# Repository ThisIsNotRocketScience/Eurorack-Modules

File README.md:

View this project on [CADLAB.io](https://cadlab.io/node/837). 

# Eurorack-Modules

This is the central repo for all the "This is not Rocket Science" eurorack modular synth modules.

Please refer to the "Production" folder if you are looking for boards to build. You will find all the design & firmware files for our latest production versions. Artwork is NOT included. Be creative. 

All our current development & experiments can be found in the "Development" folder

Sourcecode to the firmware can be found in the Eurorack-KDS repository

Tools needed:

- Eagle 7+
- Kinetis Development Studio (or whatever the latest NXP/freescale IDE is)
- A JTAG probe to flash the initial firmware

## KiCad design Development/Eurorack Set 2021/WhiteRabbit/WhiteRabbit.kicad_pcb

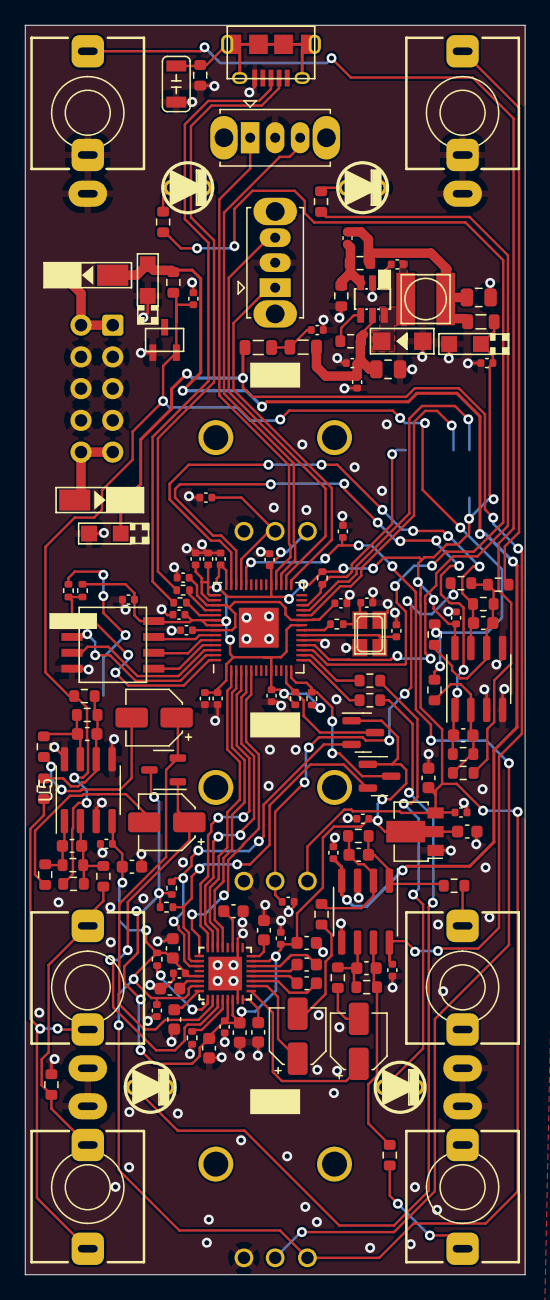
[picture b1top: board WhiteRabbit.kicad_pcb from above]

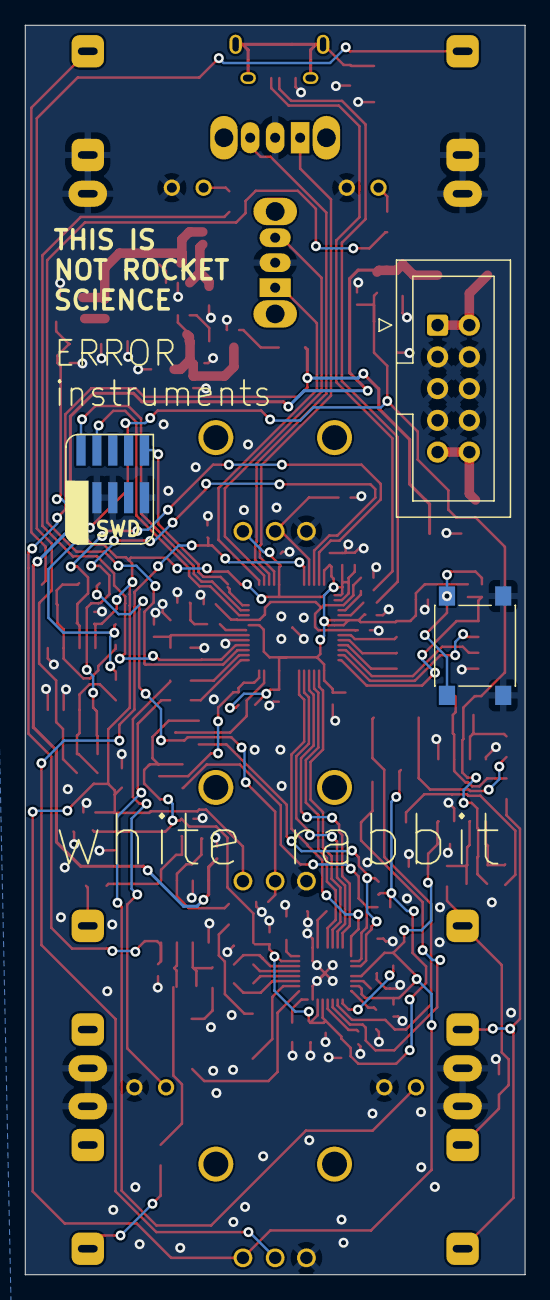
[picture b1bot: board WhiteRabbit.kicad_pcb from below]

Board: 2 copper layers, 40.0 x 100.0 mm, 146 parts (3 on the bottom side), 95 nets.

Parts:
C2, C3, C4, C7: 1u C72491; CP_Elec_4x3.9
C5, C23, C48: 197427; CASE-A_3216
C6: 1301804; C_0402_1005Metric
C8: 10u; C_0805_2012Metric
C9, C18, C19, C20, C21, C54: 4.7u; C_0603_1608Metric
C10, C12, C13, C14, C22, C52: 2.2u; C_0603_1608Metric
C11: 22u; C_0805_2012Metric
C15, C16, C56, C57, C58, C59: unknown; C_0603_1608Metric
C17, C40, C41, C42, C43, C44, C45, C46, C62, C63: 1759017; C_0402_1005Metric
C24, C50: 10u; C_0603_1608Metric
C25, C26, C27, C28, C29, C30, C31, C35, C36, C37, C38, C47, C49, C51, C53, C55, C60, C61, C99: 100n; C_0402_1005Metric
C32, C33: 27p; C_0402_1005Metric
C34, C100: 1u; C_0402_1005Metric
C39: 4.7n 100v; C3216
D1, D2: 9551824; DO-214AC
D3, D4, D5, D6: LED3MM; 3MMLED
D7: BAT54C C49991; SOT-23-3
D18: schottky; SOD123
J1: MICRO-USB-5P; C132563
J8: Conn_02x05_Odd_Even; IDC-Header_2x05_P2.54mm_Vertical
J9, J10, J11, J12, J13, J14: AudioJack2_SwitchT; Jack_3.5mm_QingPu_WQP-PJ301M-12_Vertical
L1, L2, L4: 0.1uH C76737; L_0805_2012Metric
L3: 4.7uH; L0420
Q1, Q2: TSM2302CX; SOT-23
Q4: 12mhz; NX3225
R1, R44, R45: unknown; ALPS_POT_SQUAREHOLES
R4, R6: 27; R_0402_1005Metric
R12, R13, R14, R15, R16, R17, R18, R19, R20, R21, R22, R23, R24, R25, R26, R27, R28, R29, R30, R31, R32, R35, R36, R37, R38, R39, R40, R41, R42, R43: unknown; R_0603_1608Metric
R33, R103, R105, R106: 1k; R_0402_1005Metric
R34: 10k DNP; R_0402_1005Metric
R52: 10k; R_0402_1005Metric
R74: 1M; R_0603_1608Metric
R104, R107: DNP; R_0402_1005Metric
R108, R109: 2k; R_0402_1005Metric
REF1: ALC5616-CGT; QFN-32_L4.0-W4.0-P0.40-TL-EP2.7
SW1: SW_Push; SW_Push_1P1T_NO_6x6mm_H9.5mm
SW2, SW3: SW_SPDT_MSM; SW_Slide_1P2T_CK_OS102011MS2Q
SWD2: unknown; M50-3600542
U1: 9778330; SOT95P237X112-3N
U2: AZ1117-1.8; SOT-89-3
U3: RP2040; QFN-56-1EP_7x7mm_P0.4mm_EP3.2x3.2mm
U4: TL072; SOIC-8_3.9x4.9mm_P1.27mm
U5, U6: C2937047; SOIC-8_3.9x4.9mm_P1.27mm
U$5: BL9342; SOT23-6
U$25: W25Q256JVEIQTR; SOIC-8

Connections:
+1V8: C18.1, C19.1, C20.1, C38.1, C47.1, C50.1, C51.1, D7.3, Q1.1 (G), Q2.1 (G), R105.2, R106.2, REF1.5 (DACREF), REF1.6 (AVDD), REF1.15 (CPVDD), U2.2 (VO)
+3V3: C17.1, C23.+ (1), C24.1, C25.2, C26.2, C27.2, C28.2, C30.2, C31.2, C35.2, C36.2, C37.2, C49.1, C52.2, C53.1, C54.1, C55.1, C63.1, C100.1, L4.2, R1.P$3 (A), R34.2, R44.P$3 (A), R45.P$3 (A), R52.1, R104.1, R108.2, R109.2, REF1.29 (DBVDD), REF1.31 (MICVDD), SWD2.1 (VCC), U2.3 (VI), U3.1 (IOVDD), U3.10 (IOVDD), U3.22 (IOVDD), U3.33 (IOVDD), U3.42 (IOVDD), U3.43 (ADC_AVDD), U3.44 (VREG_IN), U3.48 (USB_VDD), U3.49 (IOVDD), U5.4 (V-), U6.8 (V+), U$25.8 (VCC)
+12V: C48.+ (1), C60.1, D1.2 (-), L1.1, U4.8 (V+)
-5V: C6.2, R15.2, R19.2, R25.2, R26.2, R28.2, U1.2 (ANODE)
-12V: C5.- (2), C61.2, D2.1 (+), R26.1, U4.4 (V-)
/MCU & Eeprom/ADC_JACK_X: C16.2, R22.1, U3.40 (GPIO28_ADC2), U6.1
/MCU & Eeprom/ADC_JACK_Y: C15.2, R12.1, U3.41 (GPIO29_ADC3), U6.7
/MCU & Eeprom/ADC_KNOB_MIX: C62.1, R1.P$2 (S), U3.38 (GPIO26_ADC0)
/MCU & Eeprom/ADC_KNOB_X: C41.1, R44.P$2 (S), U3.39 (GPIO27_ADC1)
/MCU & Eeprom/BOOTSEL_BUT: R33.2, SW1.2
/MCU & Eeprom/CODEC_IN_LEFT: C4.2, R18.1
/MCU & Eeprom/CODEC_IN_LEFT_CLAMPED: C4.1, D7.1, REF1.3 (IN2P)
/MCU & Eeprom/CODEC_IN_RIGHT: C7.2, R24.1
/MCU & Eeprom/CODEC_IN_RIGHT_CLAMPED: C7.1, D7.2, REF1.2 (IN1P)
/MCU & Eeprom/CODEC_OUT_LEFT: C3.2, R35.2
/MCU & Eeprom/CODEC_OUT_RIGHT: C2.2, R27.2
/MCU & Eeprom/CODEC_SCL: Q2.2 (S), R106.1, REF1.26 (SCL)
/MCU & Eeprom/CODEC_SCL_HIGH: Q2.3 (D), R109.1, U3.14 (GPIO11)
/MCU & Eeprom/CODEC_SDA: Q1.2 (S), R105.1, REF1.27 (SDA)
/MCU & Eeprom/CODEC_SDA_HIGH: Q1.3 (D), R108.1, U3.13 (GPIO10)
/MCU & Eeprom/COREVDD: C29.1, C34.1, C99.1, U3.23 (DVDD), U3.45 (VREG_VOUT), U3.50 (DVDD)
/MCU & Eeprom/I2S_ADCDAT: REF1.21 (ADCDAT1), U3.3 (GPIO1)
/MCU & Eeprom/I2S_BCLK: REF1.24 (BCLK1), U3.4 (GPIO2)
/MCU & Eeprom/I2S_DACDAT: REF1.22 (DACDAT1), U3.2 (GPIO0)
/MCU & Eeprom/I2S_LRCK: REF1.23 (LRCK1), U3.5 (GPIO3)
/MCU & Eeprom/I2S_MCLK: REF1.25 (MCLK), U3.6 (GPIO4)
/MCU & Eeprom/JACK_DELAY: J13.T, R14.2
/MCU & Eeprom/KNOB_Y: C40.1, R38.2, R45.P$2 (S)
/MCU & Eeprom/LED_DELAYS: R41.2, U3.17 (GPIO14)
/MCU & Eeprom/LED_INPUTS: R39.2, U3.15 (GPIO12)
/MCU & Eeprom/LED_OUTPUTS: R40.2, U3.16 (GPIO13)
/MCU & Eeprom/LED_VERBS: R42.2, U3.18 (GPIO15)
/MCU & Eeprom/MEM_CLK: U3.52 (QSPI_SCLK), U$25.6 (CLK)
/MCU & Eeprom/MEM_CS: R33.1, R34.1, U3.56 (QSPI_SS), U$25.1 (/CS)
/MCU & Eeprom/MEM_IO0: U3.53 (QSPI_SD0), U$25.5 (DI)
/MCU & Eeprom/MEM_IO1: U3.55 (QSPI_SD1), U$25.2 (DO)
/MCU & Eeprom/MEM_IO2: U3.54 (QSPI_SD2), U$25.3 (IO2)
/MCU & Eeprom/MEM_IO3: U3.51 (QSPI_SD3), U$25.7 (IO3)
/MCU & Eeprom/RUN: R52.2, SWD2.10 (RESET), U3.26 (RUN)
/MCU & Eeprom/SWCLK: SWD2.4 (SWCLK), U3.24 (SWCLK)
/MCU & Eeprom/SWDIO: SWD2.2 (SWDIO), U3.25 (SWD)
/MCU & Eeprom/SWITCH_DELAY_OR_VERB_1: SW2.3, U3.31 (GPIO20)
/MCU & Eeprom/SWITCH_DELAY_OR_VERB_2: SW2.1, U3.32 (GPIO21)
/MCU & Eeprom/SWITCH_TYPE_1: SW3.1, U3.29 (GPIO18)
/MCU & Eeprom/SWITCH_TYPE_2: SW3.3, U3.30 (GPIO19)
/MCU & Eeprom/USB_N: J1.2 (DM), R6.1
/MCU & Eeprom/USB_P: J1.3 (DP), R4.1
/Power/min12in: D2.2 (-), J8.1, J8.2
/Power/plus12in: D1.1 (+), J8.9, J8.10
/Power/regulator_feedback_1: C11.2, C46.1, L3.2, L4.1, R31.1
/Power/regulator_feedback_2: C46.2, R31.2, R32.1, U$5.3 (FB)
/Power/regulator_filter: C42.2, L1.2, L2.1
/Power/regulator_inputside: C8.2, C43.2, C44.2, L2.2, R23.2, U$5.5 (VIN)
/Power/regulator_switchoutput: C45.1, D18.-, L3.1, U$5.6 (SW)
GND: C5.+ (1), C6.1, C8.1, C9.1, C11.1, C13.1, C14.1, C17.2, C18.2, C19.2, C20.2, C21.2, C22.2, C23.- (2), C24.2, C25.1, C26.1, C27.1, C28.1, C29.2, C30.1, C31.1, C32.2, C33.2, C34.2, C35.1, C36.1, C37.1, C38.2, C39.1, C40.2, C41.2, C42.1, C43.1, C44.1, C47.2, C48.- (2), C49.2, C50.2, C51.2, C52.1, C53.2, C54.2, C55.2, C60.2, C61.1, C62.2, C63.2, C99.2, C100.2, D3.1 (K), D4.1 (K), D5.1 (K), D6.1 (K), D18.+, J1.5 (GND@1), J8.3, J8.4, J8.5, J8.6, J8.7, J8.8, J9.S, J10.S, J11.S, J12.S, J13.S, J13.TN, J14.S, J14.TN, Q4.2 (G2), Q4.4 (G1), R1.P$1 (E), R32.2, R43.2, R44.P$1 (E), R45.P$1 (E), R74.1, R107.1, REF1.7 (AGND), REF1.18 (CPVREF), REF1.33 (EP), SW1.1, SW2.2, SW3.2, SWD2.3 (GND1), SWD2.5 (GND2), SWD2.9 (GND3), U1.1 (CATHODE), U2.1 (GND), U3.19 (TESTEN), U3.57 (GND), U4.3 (+), U4.5 (+), U5.3 (+), U5.5 (+), U5.8 (V+), U6.3 (+), U6.4 (V-), U6.5 (+), U$5.2 (GND), U$25.4 (GND)
unnamed: C56.2, R17.1, R18.2, U5.1
unnamed: C57.2, R20.1, R24.2, U5.7
unnamed: C58.2, R29.1, R30.2, U4.7
unnamed: C59.2, R36.1, R37.2, U4.1
unnamed: D3.2 (A), R39.1
unnamed: D4.2 (A), R40.1
unnamed: D5.2 (A), R41.1
unnamed: D6.2 (A), R42.1
unnamed: C39.2, J1.B@2 (GND@2), J1.B@4 (GND@2), J1.B@5 (GND@2), J1.B@6 (GND@3), J1.B@7 (GND@2), J1.B@8 (GND@2), J1.B@9 (GND@2), J1.B@12 (GND@2), R74.2
unnamed: J9.TN, J10.T, R21.2
unnamed: J9.T, J10.TN, R13.2, R43.1
unnamed: J11.T, R37.1
unnamed: J12.T, R30.1
unnamed: J14.T, R16.2
unnamed: C32.1, Q4.1 (X1), R103.1
unnamed: C33.1, Q4.3 (X2), U3.20 (XIN)
unnamed: C12.2, REF1.13 (CPN1)
unnamed: C10.2, REF1.11 (CPN2)
unnamed: C12.1, REF1.14 (CPP1)
unnamed: C10.1, REF1.12 (CPP2)
unnamed: C13.2, REF1.19 (CPVEE)
unnamed: C14.2, REF1.16 (CPVPP)
unnamed: C22.1, REF1.30 (DCVDD)
unnamed: R107.2, REF1.4 (IN2N/JD2)
unnamed: R104.2, REF1.1 (JD1)
unnamed: C2.1, REF1.9 (LOUTL/P)
unnamed: C3.1, REF1.10 (LOUTR/N)
unnamed: C21.1, REF1.32 (MICBIAS1)
unnamed: C9.2, REF1.8 (VREF)
unnamed: R6.2, U3.46 (USB_DM)
unnamed: R4.2, U3.47 (USB_DP)
unnamed: R103.2, U3.21 (XOUT)
unnamed: C59.1, R35.1, R36.2, U4.2 (-)
unnamed: C58.1, R27.1, R29.2, U4.6 (-)
unnamed: C56.1, R13.1, R17.2, R19.1, U5.2 (-)
unnamed: C57.1, R20.2, R21.1, R25.1, U5.6 (-)
unnamed: C16.1, R14.1, R22.2, R28.1, U6.2 (-)
unnamed: C15.1, R12.2, R15.1, R16.1, R38.1, U6.6 (-)
unnamed: C45.2, U$5.1 (BST)
unnamed: R23.1, U$5.4 (EN)

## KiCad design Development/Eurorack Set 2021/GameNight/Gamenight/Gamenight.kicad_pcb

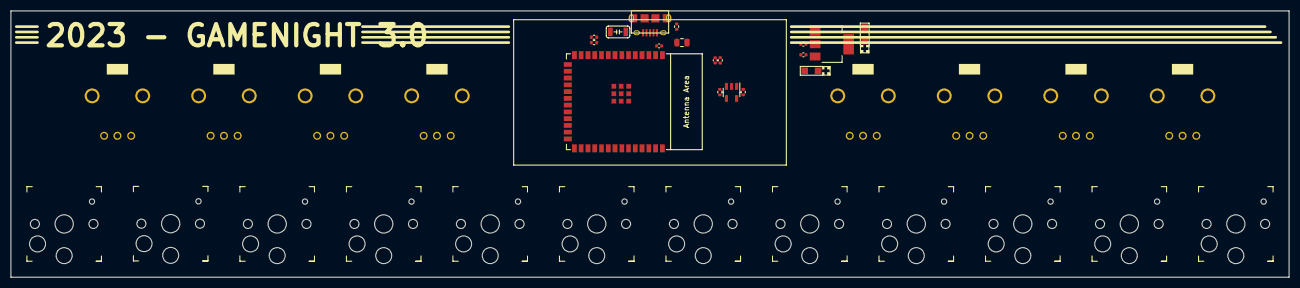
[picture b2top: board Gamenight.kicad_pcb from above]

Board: 2 copper layers, 240.0 x 50.0 mm, 39 parts (1 on the bottom side), 12 nets, no tracks yet.

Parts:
C48, C52: 1759017; C_0402_1005Metric
C50, C55: 197427; CASE-A_3216
C59: 4.7n 100v; C3216
C60: 1u; C_0402_1005Metric
C61: 22u; C_0805_2012Metric
C62: 100n; C_0402_1005Metric
J14: MICRO-USB-5P; C132563
P1, P2, P3, P4, P5, P6, P7, P8: POTSQUAREHOLE_SMALLKNOB; ALPS_POT_SQUAREHOLES
R73, R74: 0; R_0402_1005Metric
R75: 1M; R_0402_1005Metric
R76, R77: 2k; R_0402_1005Metric
R78: 10k; R_0402_1005Metric
SW1, SW3, SW4, SW5, SW6, SW7, SW8, SW9, SW10, SW11, SW12, SW13: SW_Push; Kailh_socket_PG1350
SW2: SW_Push; SW_Push_1P1T_NO_6x6mm_H9.5mm
U1: AMS1117-3.3; SOT-223-3_TabPin2
U2: AT24CS01-STUM; SOT-23-5
U12: ESP32-S3-WROOM-1

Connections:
+3V3: C48.1, C55.+ (1), C61.1, C62.1, R76.2, R77.1, R78.1, U1.2 (VO), U2.4 (VCC), U12.2 (3V3)
+5V: C50.+ (1), C52.2, J14.1 (VCC), U1.3 (VI)
/BOOTSEL_BUT: SW2.2, U12.27 (GPIO0/BOOT)
/EEPROM_SCL: R77.2, U2.1 (SCL), U12.33 (MTDO/GPIO40/CLK_OUT2)
/EEPROM_SDA: R76.1, U2.3 (SDA), U12.32 (MTCK/GPIO39/CLK_OUT3/SUBSPICS1)
/EN: C60.1, R78.2, U12.3 (EN)
/USB_N: J14.2 (DM), R74.1
/USB_P: J14.3 (DP), R73.1
GND: C48.2, C50.- (2), C52.1, C55.- (2), C59.1, C60.2, C61.2, C62.2, J14.5 (GND@1), R75.1, SW2.1, U1.1 (GND), U2.2 (GND), U2.5 (WP), U12.1 (GND), U12.40 (GND), U12.41 (GND)
unnamed: C59.2, J14.B@2 (GND@2), J14.B@4 (GND@2), J14.B@5 (GND@2), J14.B@6 (GND@3), J14.B@7 (GND@2), J14.B@8 (GND@2), J14.B@9 (GND@2), J14.B@12 (GND@2), R75.2
unnamed: R74.2, U12.13 (GPIO19/U1RTS/ADC2_CH8/CLK_OUT2/USB_D-)
unnamed: R73.2, U12.14 (GPIO20/U1CTS/ADC2_CH9/CLK_OUT1/USB_D+)

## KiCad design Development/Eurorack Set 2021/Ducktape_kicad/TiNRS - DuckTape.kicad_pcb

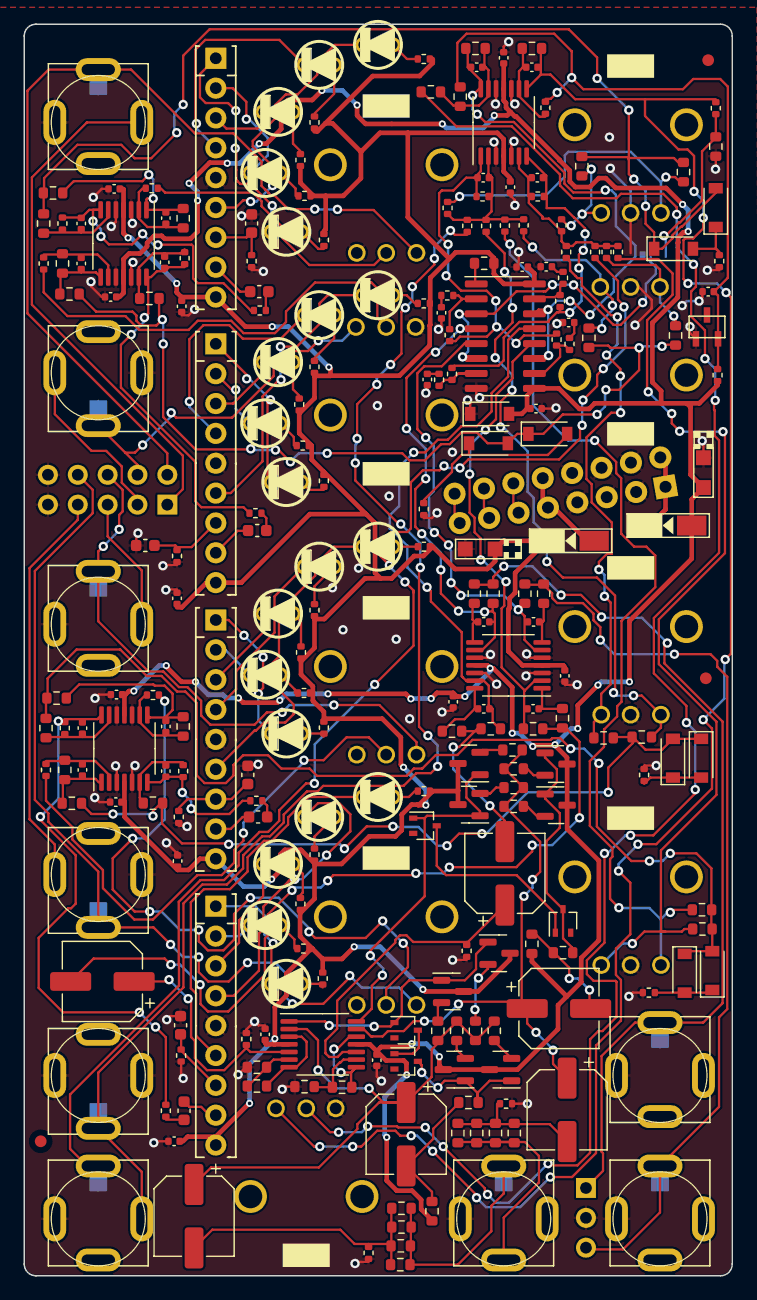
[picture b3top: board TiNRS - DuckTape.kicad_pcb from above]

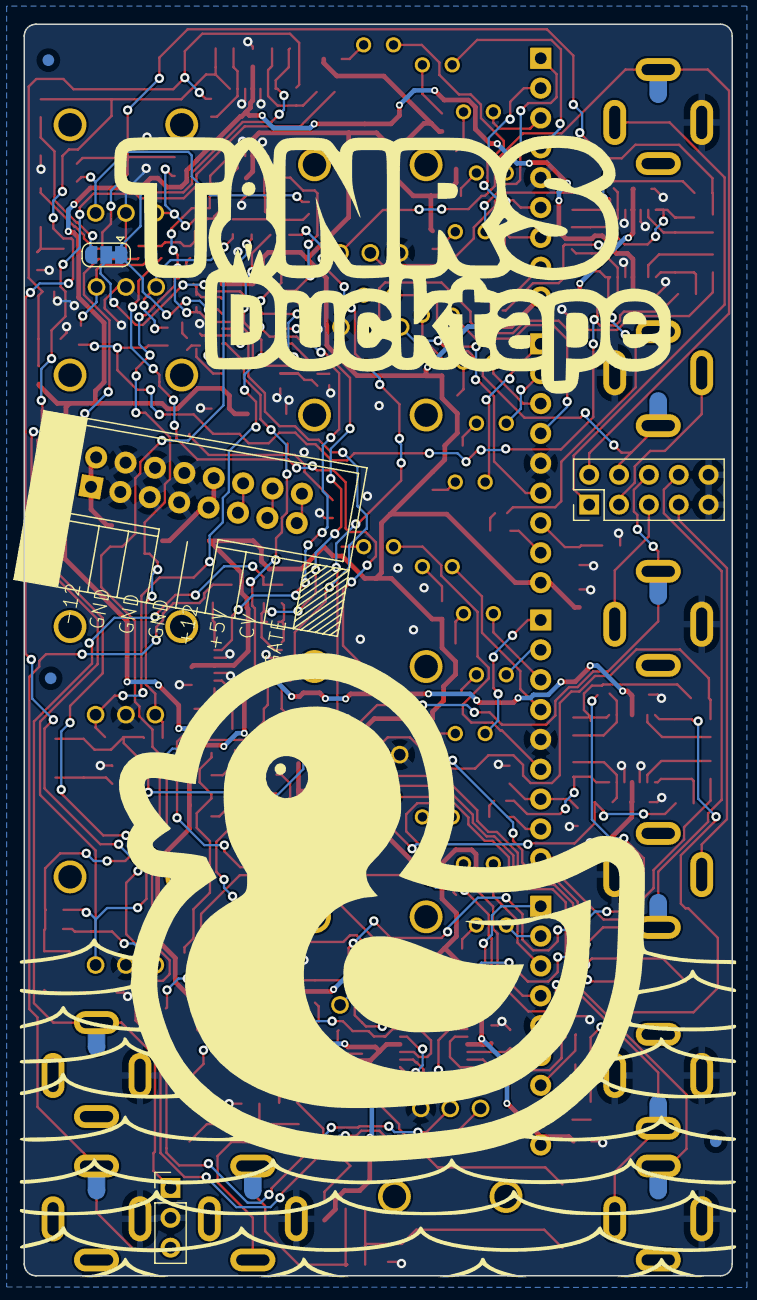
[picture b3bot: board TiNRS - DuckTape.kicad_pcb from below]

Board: 2 copper layers, 60.2 x 106.5 mm, 261 parts (7 on the bottom side), 164 nets.

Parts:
C1, C2, C3, C4, C7, C8, C9, C10, C11, C12, C13, C14, C15, C16, C17, C18, C19, C20, C21, C22, C25, C28, C31, C34, C35, C36, C37, C38, C39, C40, C41, C42, C50, C51, C52, C53: unknown; C_0402_1005Metric
C5, C48: 197427; CASE-A_3216
C6: 1301804; C_0402_1005Metric
C23, C24, C26, C27, C29, C30, C32, C33: unknown; C_0603_1608Metric
C43, C44, C45, C46, C47, C49: 100u; CP_Elec_6.3x3
D1, D2: D-SMA; DO-214AC
D3, D4, D5, D6, D7, D8, D9, D10, D11: 1N4148W; D_SOD-123
D12, D13, D14, D15, D16, D17, D18, D19, D20, D21, D22, D23, D24, D25, D26, D27, D28, D29, D30, D31: LED3MM; 3MMLED
D32, D33, D34, D35: BAS16W; SOT-323_SC-70
FID1, FID2, FID3, FID4, FID5, FID6: Fiducial; Fiducial_1mm_Mask2mm
J1: Conn_01x03; PinHeader_1x03_P2.54mm_Vertical
J2: Conn_02x05_Odd_Even; PinHeader_2x05_P2.54mm_Vertical
J14: unknown; POWER_16_SHROUDED
JACK1, JACK2, JACK3, JACK4, JACK5, JACK6, JACK7, JACK8, JACK9: AUDIO-JACK_SMALLSYMBOL; 3.5MM-JACK-SWITCH-13MM-NOHOLES-TESTPAD
JP1: SolderJumper_3_Bridged12; SolderJumper-3_P1.3mm_Bridged12_RoundedPad1.0x1.5mm
OUTLINE1: unknown; EURORACK12HPPCB
Q1, Q2, Q5, Q6: MMBT3904; SOT-23
Q3, Q4, Q7, Q8: MMBT3906; SOT-23
R1, R3, R5, R10, R11, R16, R17, R22, R23, R34, R36, R38, R40, R42, R44, R46, R48, R51, R52, R55, R56, R82, R84, R87, R90, R93, R96, R97, R98, R99, R100, R102, R103, R104, R105, R106, R107, R108, R110, R111, R112, R113, R114, R116, R117, R118, R119, R120, R121, R122, R123, R124, R125, R126, R127, R128, R129, R130: unknown; R_0603_1608Metric
R2, R7, R9, R13, R15, R19, R21, R25, R26, R27, R28, R30, R31, R32, R33, R35, R37, R39, R41, R43, R45, R47, R49, R50, R53, R54, R57, R58, R59, R60, R61, R62, R63, R64, R65, R66, R67, R68, R69, R70, R71, R72, R73, R74, R75, R76, R77, R78, R79, R80, R81, R83, R85, R86, R88, R89, R91, R92, R94, R95, R101, R109, R115, R131, R132, R133, R134: unknown; R_0402_1005Metric
R4, R6, R8, R12, R14, R18, R20, R24, R29: unknown; ALPS_POT_SQUAREHOLES
U1: 9778330; SOT95P237X112-3N
U2: SSI2164; SOIC-16_3.9x9.9mm_P1.27mm
U3, U4, U5, U10, U11: TL074; TSSOP-14_4.4x5mm_P0.65mm
U6, U7, U8, U9: KA2284; SIP9_Housing

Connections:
+10V: C22.2, R29.P$3 (A), R55.1, R81.2, U5.8
+12V: C7.2, C9.2, C15.2, C19.2, C25.1, C28.1, C31.1, C34.1, C35.2, C37.2, C48.+ (1), D1.2 (-), Q1.3 (C), Q2.3 (C), Q5.3 (C), Q6.3 (C), R1.2, R58.1, R59.1, R60.1, R61.1, R62.1, R64.1, R65.1, R66.1, R67.1, R68.1, R70.1, R71.1, R72.1, R73.1, R74.1, R76.1, R77.1, R78.1, R79.1, R80.1, U2.16 (V+), U3.4 (V+), U4.4 (V+), U5.4 (V+), U6.9 (VCC), U7.9 (VCC), U8.9 (VCC), U9.9 (VCC), U10.4 (V+), U11.4 (V+)
-5V: C6.2, R26.2, R52.2, R53.2, U1.2 (ANODE)
-12V: C5.- (2), C8.2, C10.2, C16.2, C21.2, C36.2, C38.2, D2.1 (+), D3.2 (A), Q3.3 (C), Q4.3 (C), Q7.3 (C), Q8.3 (C), R26.1, R108.2, R122.2, U2.9 (V-), U3.11 (V-), U4.11 (V-), U5.11 (V-), U10.11 (V-), U11.11 (V-)
/CHAN_1: D4.2 (A), D5.1 (K), R5.1, R84.2, R123.2, R124.2
/CHAN_2: D6.2 (A), D7.1 (K), R11.1, R87.2, R125.2, R126.2
/CHAN_3: D8.2 (A), D9.1 (K), R17.1, R90.2, R127.2, R128.2
/CHAN_4: D10.2 (A), D11.1 (K), R23.1, R93.2, R129.2, R130.2
/DEF1: J2.1, JACK2.SWITCH
/DEF2: J2.3, JACK3.SWITCH
/DEF3: J2.5, JACK4.SWITCH
/DEF4: J2.7, JACK5.SWITCH
/HEADPHONE_LEFT: C43.2, R42.1, R44.1
/HEADPHONE_RIGHT: C46.2, R46.1, R48.1
/HeadphoneAmp/LEFT_TIP: JACK1.TIP, R98.2, R99.2, R104.2, R106.2
/HeadphoneAmp/RIGHT_RING: JACK1.SECOND, R112.2, R113.2, R118.2, R120.2
/IN1: J2.2, JACK2.TIP, R4.P$3 (A)
/IN2: J2.4, JACK3.TIP, R8.P$3 (A)
/IN3: J2.6, JACK4.TIP, R14.P$3 (A)
/IN4: J2.8, JACK5.TIP, R20.P$3 (A)
/IN_LEFT: JACK7.TIP, JACK9.SWITCH, R47.1
/IN_RIGHT: JACK9.TIP, R49.2
/LEFT_BUF: C17.2, R27.2, R30.2, R50.1, U5.1
/MASTER_LEVEL: C18.2, JP1.1 (A), R51.1, U2.11 (VC3), U2.14 (VC4), U5.14
/OUT_LEFT: J1.1, JACK6.TIP, R34.1, R36.1
/OUT_RIGHT: J1.3, JACK8.TIP, R38.1, R40.1
/Power/min12in: D2.2 (-), J14.1 (-12V), J14.2 (-12V)
/Power/plus12in: D1.1 (+), J14.9 (+12V), J14.10 (+12V)
/RIGHT_BUF: C20.2, R28.2, R31.2, R54.1, U5.7
/SUM_LEFT: C17.1, R33.1, R37.1, R41.1, R45.1, R47.2, R50.2, U5.2 (-)
/SUM_RIGHT: C20.1, R32.1, R35.1, R39.1, R43.1, R49.1, R54.2, U5.6 (-)
/VCA1_OUT: C11.1, R36.2, U2.4 (I_OUT1), U4.9 (-)
/VCA2_OUT: C12.1, R40.2, U2.5 (I_OUT2), U4.6 (-)
/VCA3_OUT: C13.1, R44.2, U2.12 (I_OUT3), U4.2 (-)
/VCA4_OUT: C14.1, R48.2, U2.13 (I_OUT4), U4.13 (-)
/VUBarCircle1/Audio: C24.1, R86.2
/VUBarCircle2/Audio: C27.1, R89.2
/VUBarCircle3/Audio: C33.1, R92.2
/VUBarCircle/Audio: C30.1, R83.2
GND: C5.+ (1), C6.1, C7.1, C8.1, C9.1, C10.1, C15.1, C16.1, C19.1, C21.1, C23.2, C25.2, C26.2, C28.2, C29.2, C31.2, C32.2, C34.2, C35.1, C36.1, C37.1, C38.1, C48.- (2), C50.1, C51.1, C52.1, C53.1, D3.1 (K), J1.2, J2.9, J2.10, J14.3 (GND), J14.4 (GND), J14.5 (GND), J14.6 (GND), J14.7 (GND), J14.8 (GND), JACK1.RING, JACK2.RING, JACK3.RING, JACK4.RING, JACK5.RING, JACK6.RING, JACK7.RING, JACK7.SWITCH, JACK8.RING, JACK9.RING, R4.P$1 (E), R6.P$2 (S), R7.2, R8.P$1 (E), R12.P$2 (S), R13.2, R14.P$1 (E), R18.P$2 (S), R19.2, R20.P$1 (E), R24.P$2 (S), R25.2, R29.P$1 (E), R57.1, R63.1, R69.1, R75.1, R82.1, R95.2, R101.2, R105.2, R109.2, R115.2, R119.2, U1.1 (CATHODE), U2.8 (GND), U3.3 (+), U3.5 (+), U3.10 (+), U3.12 (+), U4.3 (+), U4.5 (+), U4.10 (+), U4.12 (+), U5.3 (+), U5.5 (+), U5.10 (+), U5.12 (+), U6.5 (GND), U7.5 (GND), U8.5 (GND), U9.5 (GND), U11.3 (+), U11.5 (+), U11.10 (+), U11.12 (+)
unnamed: C1.1, R2.1, R3.2, U3.2 (-)
unnamed: C1.2, R3.1, R5.2, U3.1
unnamed: C2.1, R9.1, R10.2, U3.9 (-)
unnamed: C2.2, R10.1, R11.2, U3.8
unnamed: C3.1, R15.1, R16.2, U11.2 (-)
unnamed: C3.2, R16.1, R17.2, U11.1
unnamed: C4.1, R21.1, R22.2, U11.9 (-)
unnamed: C4.2, R22.1, R23.2, U11.8
unnamed: C11.2, R34.2, U4.8
unnamed: C12.2, R38.2, U4.7
unnamed: C13.2, R42.2, U4.1
unnamed: C14.2, R46.2, U4.14
unnamed: C18.1, R51.2, R52.1, R56.1, U5.13 (-)
unnamed: C22.1, R53.1, R55.2, U5.9 (-)
unnamed: C23.1, R57.2, U6.7 (OUTPUT)
unnamed: C24.2, U6.8 (INPUT)
unnamed: C26.1, R63.2, U7.7 (OUTPUT)
unnamed: C27.2, U7.8 (INPUT)
unnamed: C29.1, R69.2, U8.7 (OUTPUT)
unnamed: C30.2, U8.8 (INPUT)
unnamed: C32.1, R75.2, U9.7 (OUTPUT)
unnamed: C33.2, U9.8 (INPUT)
unnamed: C39.1, R84.1, R85.2, U3.6 (-)
unnamed: C39.2, R85.1, R86.1, U3.7
unnamed: C40.1, R87.1, R88.2, U3.13 (-)
unnamed: C40.2, R88.1, R89.1, U3.14
unnamed: C41.1, R90.1, R91.2, U11.6 (-)
unnamed: C41.2, R83.1, R91.1, U11.7
unnamed: C42.1, R93.1, R94.2, U11.13 (-)
unnamed: C42.2, R92.1, R94.1, U11.14
unnamed: C43.1, R95.1, U10.5 (+)
unnamed: C44.1, C45.1, R96.2, R97.2, R102.1, R103.1, U10.2 (-)
unnamed: C44.2, R98.1, R99.1, R101.1, R104.1, R106.1
unnamed: C45.2, R107.2, R108.1
unnamed: C46.1, R109.1, U10.10 (+)
unnamed: C47.1, C49.1, R110.2, R111.2, R116.1, R117.1, U10.13 (-)
unnamed: C47.2, R112.1, R113.1, R115.1, R118.1, R120.1
unnamed: C49.2, R121.2, R122.1
unnamed: C50.2, R131.2
unnamed: C51.2, R132.2
unnamed: C52.2, R133.2
unnamed: C53.2, R134.2
unnamed: D4.1 (K), D5.2 (A), R7.1
unnamed: D6.1 (K), D7.2 (A), R13.1
unnamed: D8.1 (K), D9.2 (A), R19.1
unnamed: D10.1 (K), D11.2 (A), R25.1
unnamed: D12.2 (A), R58.2
unnamed: D13.2 (A), R59.2
unnamed: D14.2 (A), R60.2
unnamed: D15.2 (A), R61.2
unnamed: D16.2 (A), R62.2
unnamed: D17.2 (A), R64.2
unnamed: D18.2 (A), R65.2
unnamed: D19.2 (A), R66.2
unnamed: D20.2 (A), R67.2
unnamed: D21.2 (A), R68.2
unnamed: D22.2 (A), R70.2
unnamed: D23.2 (A), R71.2
unnamed: D24.2 (A), R72.2
unnamed: D25.2 (A), R73.2
unnamed: D26.2 (A), R74.2
unnamed: D27.2 (A), R76.2
unnamed: D28.2 (A), R77.2
unnamed: D29.2 (A), R78.2
unnamed: D30.2 (A), R79.2
unnamed: D31.2 (A), R80.2
unnamed: D32.1 (A), Q1.1 (B), Q2.1 (B), U10.1
unnamed: D32.3 (K), D33.1 (A)
unnamed: D33.3 (K), Q3.1 (B), Q4.1 (B), R107.1
unnamed: D34.1 (A), Q5.1 (B), Q6.1 (B), U10.14
unnamed: D34.3 (K), D35.1 (A)
unnamed: D35.3 (K), Q7.1 (B), Q8.1 (B), R121.1
unnamed: JP1.2 (C), U2.3 (VC1), U2.6 (VC2)
unnamed: JP1.3 (B), R81.1, R82.2
unnamed: Q1.2 (E), R96.1
unnamed: Q2.2 (E), R97.1
unnamed: Q3.2 (E), R102.2
unnamed: Q4.2 (E), R103.2
unnamed: Q5.2 (E), R110.1
unnamed: Q6.2 (E), R111.1
unnamed: Q7.2 (E), R116.2
unnamed: Q8.2 (E), R117.2
unnamed: R1.1, U2.1 (MODE)
unnamed: R2.2, R4.P$2 (S)
unnamed: R8.P$2 (S), R9.2
unnamed: R12.P$1 (E), R35.2, R125.1
unnamed: R12.P$3 (A), R37.2, R126.1
unnamed: R14.P$2 (S), R15.2
unnamed: R20.P$2 (S), R21.2
unnamed: R27.1, R131.1, U2.2 (I_IN1)
unnamed: R28.1, R132.1, U2.7 (I_IN2)
unnamed: R29.P$2 (S), R56.2
unnamed: R30.1, R133.1, U2.10 (I_IN3)
unnamed: R31.1, R134.1, U2.15 (I_IN4)
unnamed: R100.1, R105.1, U10.6 (-)
unnamed: R100.2, U10.3 (+), U10.7
unnamed: R114.1, R119.1, U10.9 (-)
unnamed: R114.2, U10.8, U10.12 (+)
unnamed: R6.P$1 (E), R32.2, R123.1
unnamed: R6.P$3 (A), R33.2, R124.1
unnamed: R18.P$1 (E), R39.2, R127.1
unnamed: R18.P$3 (A), R41.2, R128.1
unnamed: R24.P$1 (E), R43.2, R129.1
unnamed: R24.P$3 (A), R45.2, R130.1
unnamed: D12.1 (K), U6.1 (LED1)
unnamed: D13.1 (K), U6.2 (LED2)
unnamed: D14.1 (K), U6.3 (LED3)
unnamed: D15.1 (K), U6.4 (LED4)
unnamed: D16.1 (K), U6.6 (LED5)
unnamed: D17.1 (K), U7.1 (LED1)
unnamed: D18.1 (K), U7.2 (LED2)
unnamed: D19.1 (K), U7.3 (LED3)
unnamed: D20.1 (K), U7.4 (LED4)
unnamed: D21.1 (K), U7.6 (LED5)
unnamed: D22.1 (K), U8.1 (LED1)
unnamed: D23.1 (K), U8.2 (LED2)
unnamed: D24.1 (K), U8.3 (LED3)
unnamed: D25.1 (K), U8.4 (LED4)
unnamed: D26.1 (K), U8.6 (LED5)
unnamed: D27.1 (K), U9.1 (LED1)
unnamed: D28.1 (K), U9.2 (LED2)
unnamed: D29.1 (K), U9.3 (LED3)
unnamed: D30.1 (K), U9.4 (LED4)
unnamed: D31.1 (K), U9.6 (LED5)

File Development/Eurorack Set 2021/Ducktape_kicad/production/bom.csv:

Designator,Footprint,Quantity,Value,LCSC Part #
D2,DO-214AC,1,C8678,
D1,DO-214AC,1,C8678,
C45,CP_Elec_6.3x3,1,100u,
C49,CP_Elec_6.3x3,1,100u,
C43,CP_Elec_6.3x3,1,100u,
C46,CP_Elec_6.3x3,1,100u,
C47,CP_Elec_6.3x3,1,100u,
C44,CP_Elec_6.3x3,1,100u,
C33,C_0603_1608Metric,1,2.2u,
C32,C_0603_1608Metric,1,10u,
C30,C_0603_1608Metric,1,2.2u,
C29,C_0603_1608Metric,1,10u,
C27,C_0603_1608Metric,1,2.2u,
C26,C_0603_1608Metric,1,10u,
C24,C_0603_1608Metric,1,2.2u,
C23,C_0603_1608Metric,1,10u,
C6,C_0402_1005Metric,1,100nF,
C53,C_0402_1005Metric,1,560p,
C52,C_0402_1005Metric,1,560p,
C51,C_0402_1005Metric,1,560p,
C50,C_0402_1005Metric,1,560p,
C42,C_0402_1005Metric,1,33p,
C41,C_0402_1005Metric,1,33p,
C40,C_0402_1005Metric,1,33p,
C39,C_0402_1005Metric,1,33p,
C38,C_0402_1005Metric,1,100n,
C37,C_0402_1005Metric,1,100n,
C36,C_0402_1005Metric,1,100n,
C35,C_0402_1005Metric,1,100n,
C34,C_0402_1005Metric,1,100n,
C31,C_0402_1005Metric,1,100n,
C28,C_0402_1005Metric,1,100n,
C25,C_0402_1005Metric,1,100n,
C22,C_0402_1005Metric,1,33p,
C21,C_0402_1005Metric,1,100n,
C20,C_0402_1005Metric,1,33p,
C19,C_0402_1005Metric,1,100n,
C18,C_0402_1005Metric,1,33p,
C17,C_0402_1005Metric,1,33p,
C16,C_0402_1005Metric,1,100n,
C15,C_0402_1005Metric,1,100n,
C14,C_0402_1005Metric,1,33p,
C13,C_0402_1005Metric,1,33p,
C12,C_0402_1005Metric,1,33p,
C11,C_0402_1005Metric,1,33p,
C10,C_0402_1005Metric,1,100n,
C9,C_0402_1005Metric,1,100n,
C8,C_0402_1005Metric,1,100n,
C7,C_0402_1005Metric,1,100n,
C4,C_0402_1005Metric,1,33p,
C3,C_0402_1005Metric,1,33p,
C2,C_0402_1005Metric,1,33p,
C1,C_0402_1005Metric,1,33p,
R27,R_0402_1005Metric,1,30k,
R134,R_0402_1005Metric,1,500,
R133,R_0402_1005Metric,1,500,
R132,R_0402_1005Metric,1,500,
R131,R_0402_1005Metric,1,500,
R92,R_0402_1005Metric,1,56,
R89,R_0402_1005Metric,1,56,
R86,R_0402_1005Metric,1,56,
R83,R_0402_1005Metric,1,56,
R80,R_0402_1005Metric,1,68,
R79,R_0402_1005Metric,1,68,
R78,R_0402_1005Metric,1,68,
R77,R_0402_1005Metric,1,68,
R76,R_0402_1005Metric,1,68,
R74,R_0402_1005Metric,1,68,
R73,R_0402_1005Metric,1,68,
R72,R_0402_1005Metric,1,68,
R71,R_0402_1005Metric,1,68,
R70,R_0402_1005Metric,1,68,
R68,R_0402_1005Metric,1,68,
R67,R_0402_1005Metric,1,68,
R66,R_0402_1005Metric,1,68,
R65,R_0402_1005Metric,1,68,
R64,R_0402_1005Metric,1,68,
R62,R_0402_1005Metric,1,68,
R61,R_0402_1005Metric,1,68,
R60,R_0402_1005Metric,1,68,
R59,R_0402_1005Metric,1,68,
R58,R_0402_1005Metric,1,68,
R25,R_0402_1005Metric,1,56,
R19,R_0402_1005Metric,1,56,
R13,R_0402_1005Metric,1,56,
R7,R_0402_1005Metric,1,56,
R115,R_0402_1005Metric,1,100k,
R109,R_0402_1005Metric,1,10k,
R101,R_0402_1005Metric,1,100k,
R95,R_0402_1005Metric,1,10k,
R94,R_0402_1005Metric,1,100k,
R91,R_0402_1005Metric,1,100k,
R88,R_0402_1005Metric,1,100k,
R85,R_0402_1005Metric,1,100k,
R81,R_0402_1005Metric,1,10k,
R75,R_0402_1005Metric,1,10k,
R69,R_0402_1005Metric,1,10k,
R63,R_0402_1005Metric,1,10k,
R57,R_0402_1005Metric,1,10k,
R54,R_0402_1005Metric,1,30k,
R53,R_0402_1005Metric,1,10k,
R50,R_0402_1005Metric,1,30k,
R49,R_0402_1005Metric,1,30k,
R47,R_0402_1005Metric,1,30k,
R45,R_0402_1005Metric,1,30k,
R43,R_0402_1005Metric,1,30k,
R41,R_0402_1005Metric,1,30k,
R39,R_0402_1005Metric,1,30k,
R37,R_0402_1005Metric,1,30k,
R35,R_0402_1005Metric,1,30k,
R33,R_0402_1005Metric,1,30k,
R32,R_0402_1005Metric,1,30k,
R31,R_0402_1005Metric,1,30k,
R30,R_0402_1005Metric,1,30k,
R28,R_0402_1005Metric,1,30k,
R26,R_0402_1005Metric,1,10k,
R21,R_0402_1005Metric,1,100k,
R15,R_0402_1005Metric,1,100k,
R9,R_0402_1005Metric,1,100k,
R2,R_0402_1005Metric,1,100k,
R99,R_0603_1608Metric,1,120,
R130,R_0603_1608Metric,1,1k,
R129,R_0603_1608Metric,1,1k,
R128,R_0603_1608Metric,1,1k,
R127,R_0603_1608Metric,1,1k,
R126,R_0603_1608Metric,1,1k,
R125,R_0603_1608Metric,1,1k,
R124,R_0603_1608Metric,1,1k,
R123,R_0603_1608Metric,1,1k,
R122,R_0603_1608Metric,1,4.7k,
R121,R_0603_1608Metric,1,4.7k,
R120,R_0603_1608Metric,1,120,
R119,R_0603_1608Metric,1,470,
R118,R_0603_1608Metric,1,120,
R117,R_0603_1608Metric,1,10,
R116,R_0603_1608Metric,1,10,
R114,R_0603_1608Metric,1,2.2k,
R113,R_0603_1608Metric,1,120,
R112,R_0603_1608Metric,1,120,
R111,R_0603_1608Metric,1,10,
R110,R_0603_1608Metric,1,10,
R108,R_0603_1608Metric,1,4.7k,
R107,R_0603_1608Metric,1,4.7k,
R106,R_0603_1608Metric,1,120,
R105,R_0603_1608Metric,1,470,
R104,R_0603_1608Metric,1,120,
R103,R_0603_1608Metric,1,10,
R102,R_0603_1608Metric,1,10,
R100,R_0603_1608Metric,1,2.2k,
R98,R_0603_1608Metric,1,120,
R97,R_0603_1608Metric,1,10,
R96,R_0603_1608Metric,1,10,
R93,R_0603_1608Metric,1,43k,
R90,R_0603_1608Metric,1,43k,
R87,R_0603_1608Metric,1,43k,
R84,R_0603_1608Metric,1,43k,
R82,R_0603_1608Metric,1,15k,
R56,R_0603_1608Metric,1,200k,
R55,R_0603_1608Metric,1,20k,
R52,R_0603_1608Metric,1,110k,
R51,R_0603_1608Metric,1,110k,
R48,R_0603_1608Metric,1,150k,
R46,R_0603_1608Metric,1,100,
R44,R_0603_1608Metric,1,150k,
R42,R_0603_1608Metric,1,100,
R40,R_0603_1608Metric,1,150k,
R38,R_0603_1608Metric,1,100,
R36,R_0603_1608Metric,1,150k,
R34,R_0603_1608Metric,1,100,
R23,R_0603_1608Metric,1,2k,
R22,R_0603_1608Metric,1,33k,
R17,R_0603_1608Metric,1,2k,
R16,R_0603_1608Metric,1,33k,
R11,R_0603_1608Metric,1,2k,
R10,R_0603_1608Metric,1,33k,
R5,R_0603_1608Metric,1,2k,
R3,R_0603_1608Metric,1,33k,
R1,R_0603_1608Metric,1,7.5k,
R29,ALPS_POT_SQUAREHOLES,1,100kB,
R24,ALPS_POT_SQUAREHOLES,1,100kB,
R20,ALPS_POT_SQUAREHOLES,1,10kB,
R18,ALPS_POT_SQUAREHOLES,1,100kB,
R14,ALPS_POT_SQUAREHOLES,1,10kB,
R12,ALPS_POT_SQUAREHOLES,1,100kB,
R8,ALPS_POT_SQUAREHOLES,1,10kB,
R6,ALPS_POT_SQUAREHOLES,1,100kB,
R4,ALPS_POT_SQUAREHOLES,1,10kB,
OUTLINE1,EURORACK12HPPCB,1,EURORACK_PCB12HP,
JACK9,3.5MM-JACK-SWITCH-13MM-NOHOLES-TESTPAD,1,AUDIO-JACK_SMALLSYMBOL,
JACK8,3.5MM-JACK-SWITCH-13MM-NOHOLES-TESTPAD,1,AUDIO-JACK_SMALLSYMBOL,
JACK7,3.5MM-JACK-SWITCH-13MM-NOHOLES-TESTPAD,1,AUDIO-JACK_SMALLSYMBOL,
JACK6,3.5MM-JACK-SWITCH-13MM-NOHOLES-TESTPAD,1,AUDIO-JACK_SMALLSYMBOL,
JACK5,3.5MM-JACK-SWITCH-13MM-NOHOLES-TESTPAD,1,AUDIO-JACK_SMALLSYMBOL,
JACK4,3.5MM-JACK-SWITCH-13MM-NOHOLES-TESTPAD,1,AUDIO-JACK_SMALLSYMBOL,
JACK3,3.5MM-JACK-SWITCH-13MM-NOHOLES-TESTPAD,1,AUDIO-JACK_SMALLSYMBOL,
JACK2,3.5MM-JACK-SWITCH-13MM-NOHOLES-TESTPAD,1,AUDIO-JACK_SMALLSYMBOL,
JACK1,3.5MM-JACK-SWITCH-13MM-NOHOLES-TESTPAD,1,AUDIO-JACK_SMALLSYMBOL,
J14,POWER_16_SHROUDED,1,POWERSHROUDED,
C48,CASE-A_3216,1,10uF,
C5,CASE-A_3216,1,10uF,
U10,TSSOP-14_4.4x5mm_P0.65mm,1,TL074,
U11,TSSOP-14_4.4x5mm_P0.65mm,1,TL074,
Q5,SOT-23,1,MMBT3904,
D16,3MMLED,1,LED3MM,
D5,D_SOD-123,1,1N4148W,
U9,SIP9_Housing,1,KA2284,
Q8,SOT-23,1,MMBT3906,
D8,D_SOD-123,1,1N4148W,
D35,SOT-323_SC-70,1,BAS16W,
D9,D_SOD-123,1,1N4148W,
FID6,Fiducial_1mm_Mask2mm,1,Fiducial,
Q2,SOT-23,1,MMBT3904,
FID2,Fiducial_1mm_Mask2mm,1,Fiducial,
D27,3MMLED,1,LED3MM,
U3,TSSOP-14_4.4x5mm_P0.65mm,1,TL074,
D19,3MMLED,1,LED3MM,
U4,TSSOP-14_4.4x5mm_P0.65mm,1,TL074,
Q3,SOT-23,1,MMBT3906,
U1,SOT95P237X112-3N,1,LM4040DIM3-5.0,
D22,3MMLED,1,LED3MM,
D30,3MMLED,1,LED3MM,
U6,SIP9_Housing,1,KA2284,
D7,D_SOD-123,1,1N4148W,
D29,3MMLED,1,LED3MM,
D28,3MMLED,1,LED3MM,
Q1,SOT-23,1,MMBT3904,
D24,3MMLED,1,LED3MM,
D6,D_SOD-123,1,1N4148W,
D17,3MMLED,1,LED3MM,
D25,3MMLED,1,LED3MM,
D11,D_SOD-123,1,1N4148W,
D26,3MMLED,1,LED3MM,
U5,TSSOP-14_4.4x5mm_P0.65mm,1,TL074,
D3,D_SOD-123,1,1N4148W,
D4,D_SOD-123,1,1N4148W,
D10,D_SOD-123,1,1N4148W,
D32,SOT-323_SC-70,1,BAS16W,
Q4,SOT-23,1,MMBT3906,
D12,3MMLED,1,LED3MM,
Q7,SOT-23,1,MMBT3906,
D31,3MMLED,1,LED3MM,
U2,SOIC-16_3.9x9.9mm_P1.27mm,1,SSI2164,
D20,3MMLED,1,LED3MM,
D15,3MMLED,1,LED3MM,
D13,3MMLED,1,LED3MM,
Q6,SOT-23,1,MMBT3904,
D18,3MMLED,1,LED3MM,
D23,3MMLED,1,LED3MM,
U8,SIP9_Housing,1,KA2284,
D34,SOT-323_SC-70,1,BAS16W,
U7,SIP9_Housing,1,KA2284,
D33,SOT-323_SC-70,1,BAS16W,
FID1,Fiducial_1mm_Mask2mm,1,Fiducial,
D14,3MMLED,1,LED3MM,
D21,3MMLED,1,LED3MM,
FID5,Fiducial_1mm_Mask2mm,1,Fiducial,
FID3,Fiducial_1mm_Mask2mm,1,Fiducial,
FID4,Fiducial_1mm_Mask2mm,1,Fiducial,
J2,PinHeader_2x05_P2.54mm_Vertical,1,Conn_02x05_Odd_Even,
J1,PinHeader_1x03_P2.54mm_Vertical,1,Conn_01x03,
JP1,SolderJumper-3_P1.3mm_Bridged12_RoundedPad1.0x1.5mm,1,SolderJumper_3_Bridged12,
